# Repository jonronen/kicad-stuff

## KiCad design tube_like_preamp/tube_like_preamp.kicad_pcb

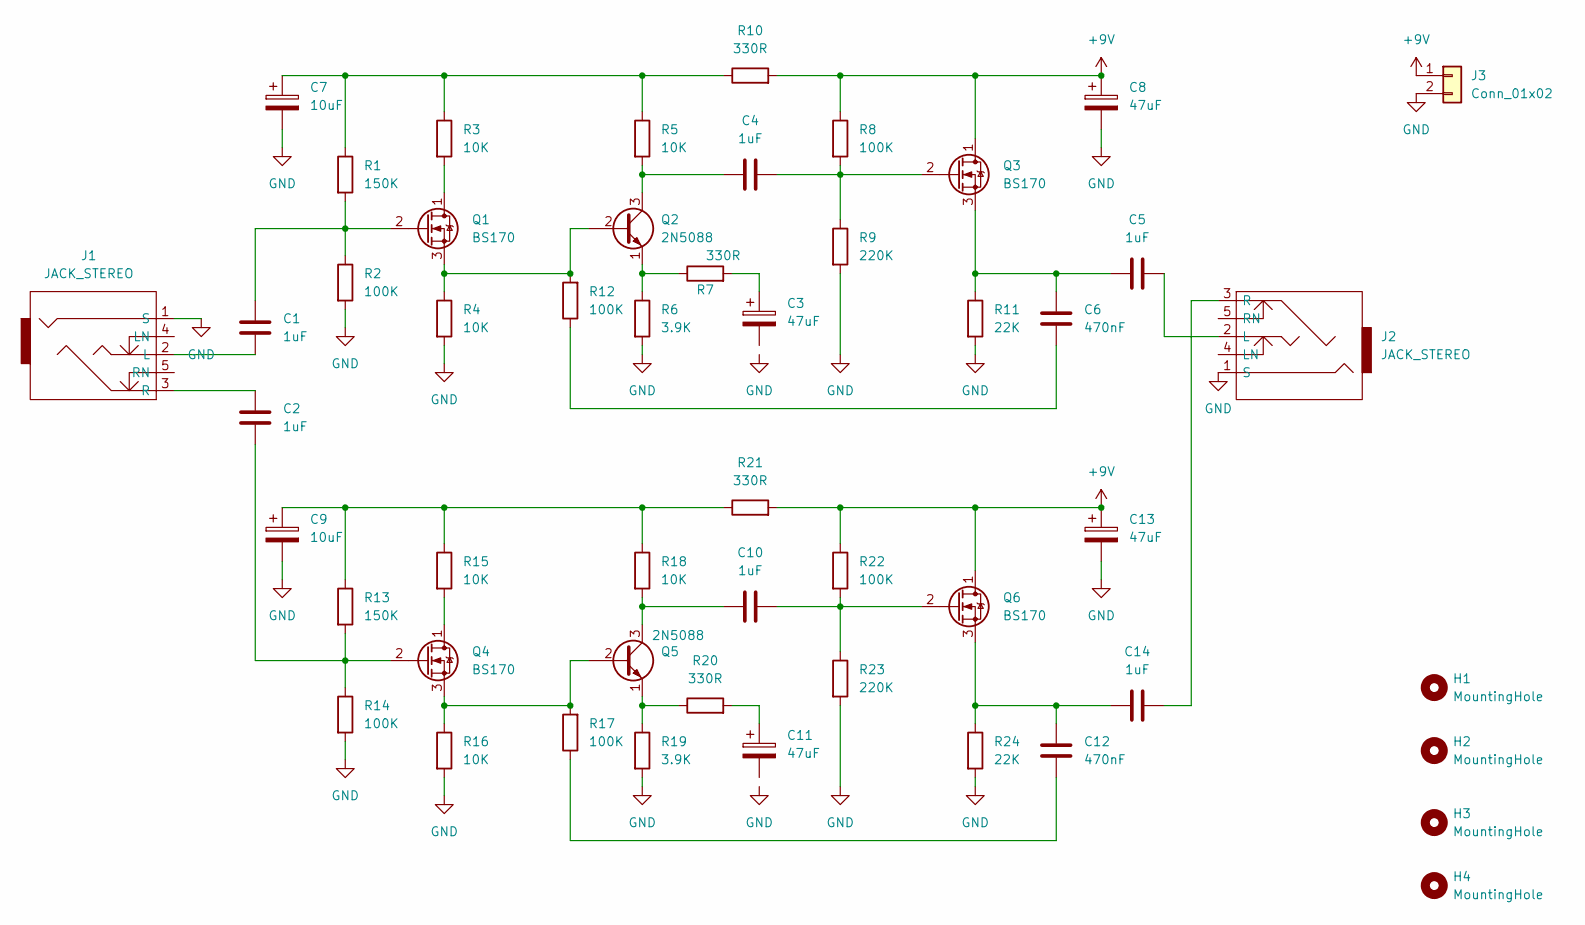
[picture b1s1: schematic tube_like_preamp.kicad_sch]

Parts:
C1, C2, C4, C5, C10, C14: 1uF; C_Disc_D4.7mm_W2.5mm_P5.00mm
C3, C8, C11, C13: 47uF; CP_Radial_D5.0mm_P2.50mm
C6, C12: 470nF; C_Disc_D4.7mm_W2.5mm_P5.00mm
C7, C9: 10uF; CP_Radial_D5.0mm_P2.50mm
H1, H2, H3, H4: MountingHole; MountingHole_3.2mm_M3_DIN965
J1, J2: JACK_STEREO; AUDIO_STEREO_CONN
J3: Conn_01x02; PinHeader_1x02_P2.54mm_Vertical
Q1, Q3, Q4, Q6: BS170; TO-92_Inline
Q2, Q5: 2N5088; TO-92_Inline
R1, R13: 150K; R_Axial_DIN0309_L9.0mm_D3.2mm_P2.54mm_Vertical
R2, R8, R12, R14, R17, R22: 100K; R_Axial_DIN0309_L9.0mm_D3.2mm_P2.54mm_Vertical
R3, R4, R5, R15, R16, R18: 10K; R_Axial_DIN0309_L9.0mm_D3.2mm_P2.54mm_Vertical
R6, R19: 3.9K; R_Axial_DIN0309_L9.0mm_D3.2mm_P2.54mm_Vertical
R7, R10, R20, R21: 330R; R_Axial_DIN0309_L9.0mm_D3.2mm_P2.54mm_Vertical
R9, R23: 220K; R_Axial_DIN0309_L9.0mm_D3.2mm_P2.54mm_Vertical
R11, R24: 22K; R_Axial_DIN0309_L9.0mm_D3.2mm_P2.54mm_Vertical

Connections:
+9V: C8.1, C13.1, J3.1, Q3.1 (D), Q6.1 (D), R8.1, R10.2, R21.2, R22.1
GND: C7.2, C8.2, C9.2, C13.2, J1.1 (S), J2.1 (S), J3.2, R2.2, R4.2, R6.2, R9.2, R11.2, R14.2, R16.2, R19.2, R23.2, R24.2
unnamed: C3.1, R7.2
unnamed: C6.1, R12.1
unnamed: C7.1, R1.1, R3.1, R5.1, R10.1
unnamed: C9.1, R13.1, R15.1, R18.1, R21.1
unnamed: C11.1, R20.2
unnamed: C12.1, R17.1
unnamed: C1.1, J1.2 (L)
unnamed: C2.2, J1.3 (R)
unnamed: C5.1, J2.2 (L)
unnamed: C14.1, J2.3 (R)
unnamed: Q1.1 (D), R3.2
unnamed: C1.2, Q1.2 (G), R1.2, R2.1
unnamed: Q1.3 (S), Q2.2 (B), R4.1, R12.2
unnamed: C4.2, Q2.3 (C), R5.2
unnamed: Q2.1 (E), R6.1, R7.1
unnamed: C4.1, Q3.2 (G), R8.2, R9.1
unnamed: C5.2, C6.2, Q3.3 (S), R11.1
unnamed: Q4.1 (D), R15.2
unnamed: C2.1, Q4.2 (G), R13.2, R14.1
unnamed: Q4.3 (S), Q5.2 (B), R16.1, R17.2
unnamed: C10.2, Q5.3 (C), R18.2
unnamed: Q5.1 (E), R19.1, R20.1
unnamed: C10.1, Q6.2 (G), R22.2, R23.1
unnamed: C12.2, C14.2, Q6.3 (S), R24.1

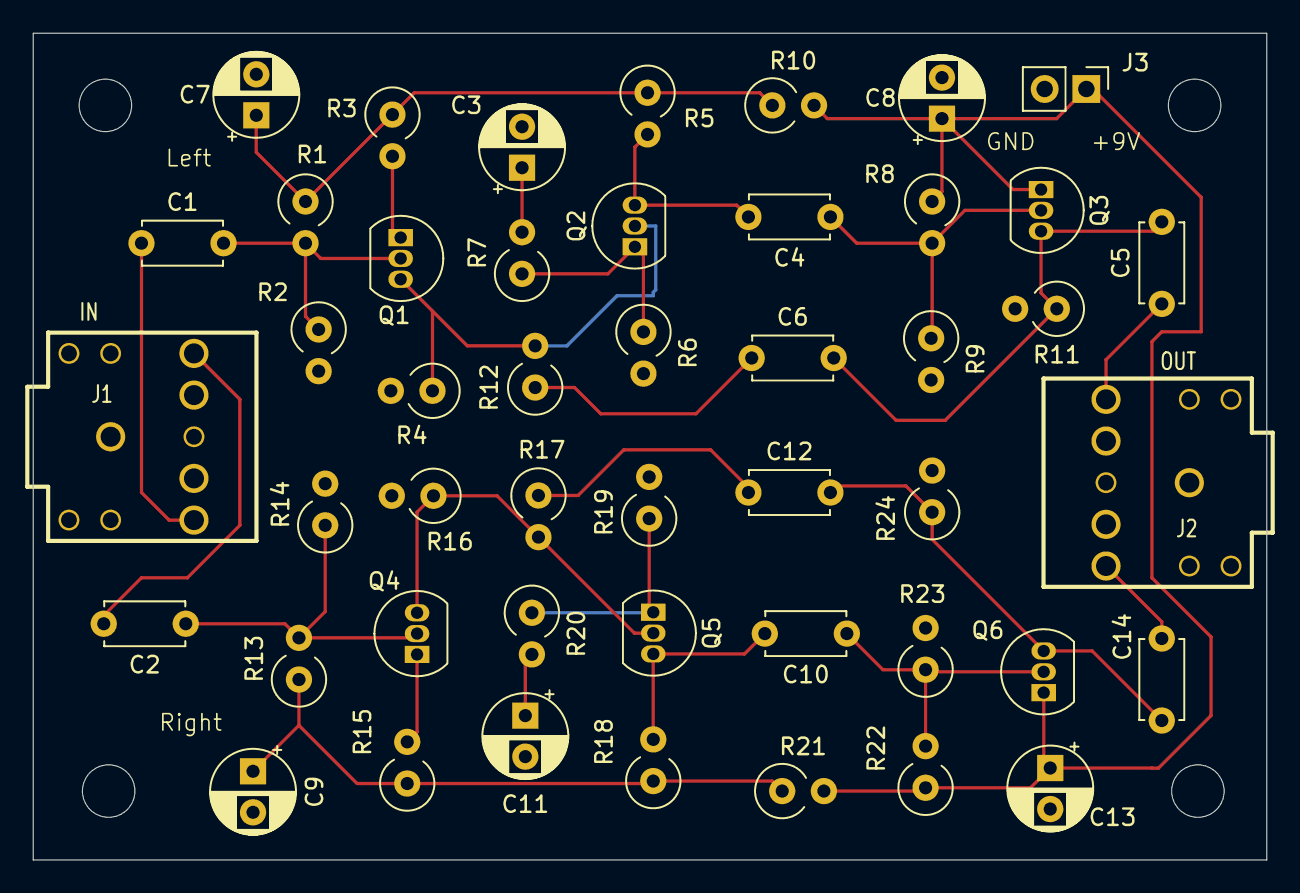
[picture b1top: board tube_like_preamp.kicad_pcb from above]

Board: 2 copper layers, 75.2 x 50.4 mm, 51 parts (0 on the bottom side), 26 nets.

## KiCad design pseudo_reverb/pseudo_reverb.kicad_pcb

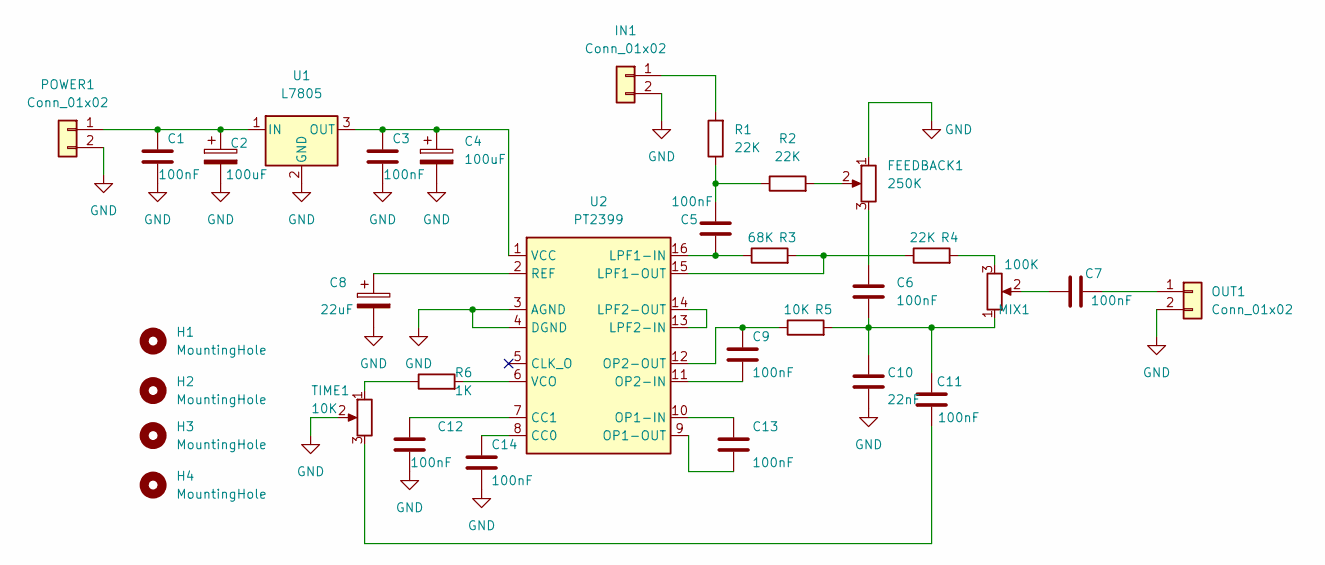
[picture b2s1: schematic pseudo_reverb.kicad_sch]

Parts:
C1, C3, C5, C6, C7, C9, C11, C12, C13, C14: 100nF; C_Disc_D3.0mm_W1.6mm_P2.50mm
C2, C4: 100uF; CP_Radial_D5.0mm_P2.50mm
C8: 22uF; CP_Radial_D5.0mm_P2.50mm
C10: 22nF; C_Disc_D3.0mm_W1.6mm_P2.50mm
FEEDBACK1: 250K; Potentiometer_Alps_RK163_Single_Horizontal
H1, H2, H3, H4: MountingHole; MountingHole_3.2mm_M3_DIN965
IN1: Conn_01x02; Molex_KK-254_AE-6410-02A_1x02_P2.54mm_Vertical
MIX1: 100K; Potentiometer_Alps_RK163_Single_Horizontal
OUT1: Conn_01x02; Molex_KK-254_AE-6410-02A_1x02_P2.54mm_Vertical
POWER1: Conn_01x02; Molex_KK-254_AE-6410-02A_1x02_P2.54mm_Vertical
R1, R2, R4: 22K; C_Disc_D3.0mm_W1.6mm_P2.50mm
R3: 68K; C_Disc_D3.0mm_W1.6mm_P2.50mm
R5: 10K; C_Disc_D3.0mm_W1.6mm_P2.50mm
R6: 1K; C_Disc_D3.0mm_W1.6mm_P2.50mm
TIME1: 10K; Potentiometer_Alps_RK163_Single_Horizontal
U1: L7805; TO-220-3_Vertical
U2: PT2399; DIP-16_W7.62mm

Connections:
GND: C1.2, C2.2, C3.2, C4.2, C8.2, C10.2, C12.2, C14.2, FEEDBACK1.1, IN1.2, OUT1.2, POWER1.2, TIME1.2, U1.2 (GND), U2.3 (AGND), U2.4 (DGND)
unnamed: C1.1, C2.1, POWER1.1, U1.1 (IN)
unnamed: C3.1, C4.1, U1.3 (OUT), U2.1 (VCC)
unnamed: C5.1, R1.1, R2.1
unnamed: C5.2, R3.1, U2.16 (LPF1-IN)
unnamed: C6.1, FEEDBACK1.3
unnamed: C7.1, MIX1.2
unnamed: C7.2, OUT1.1
unnamed: C8.1, U2.2 (REF)
unnamed: C9.1, R5.1, U2.12 (OP2-OUT)
unnamed: C9.2, U2.11 (OP2-IN)
unnamed: C6.2, C10.1, C11.2, MIX1.1, R5.2
unnamed: C11.1, TIME1.3
unnamed: C12.1, U2.7 (CC1)
unnamed: C13.1, U2.10 (OP1-IN)
unnamed: C13.2, U2.9 (OP1-OUT)
unnamed: C14.1, U2.8 (CC0)
unnamed: FEEDBACK1.2, R2.2
unnamed: IN1.1, R1.2
unnamed: MIX1.3, R4.2
unnamed: R3.2, R4.1, U2.15 (LPF1-OUT)
unnamed: R6.1, TIME1.1
unnamed: R6.2, U2.6 (VCO)
unnamed: U2.13 (LPF2-IN), U2.14 (LPF2-OUT)

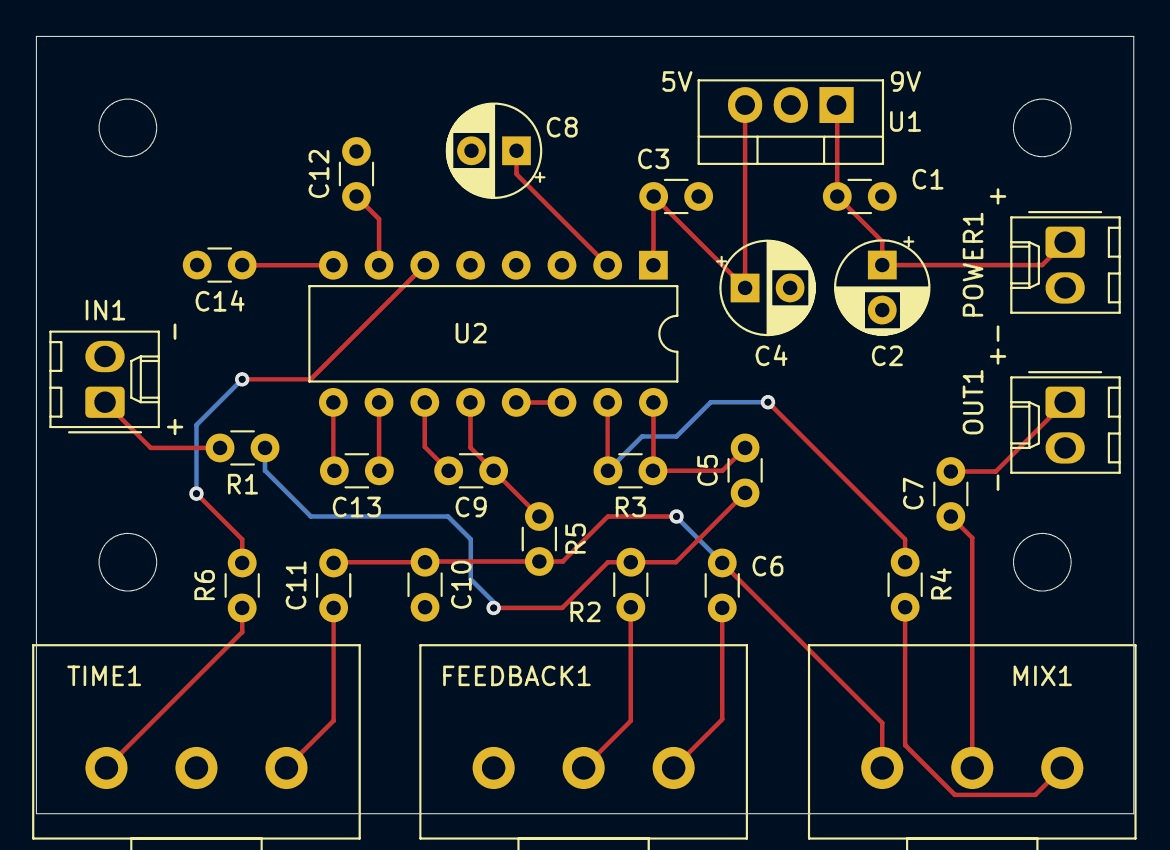
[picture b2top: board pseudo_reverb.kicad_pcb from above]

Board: 2 copper layers, 61.0 x 43.2 mm, 32 parts (0 on the bottom side), 24 nets.

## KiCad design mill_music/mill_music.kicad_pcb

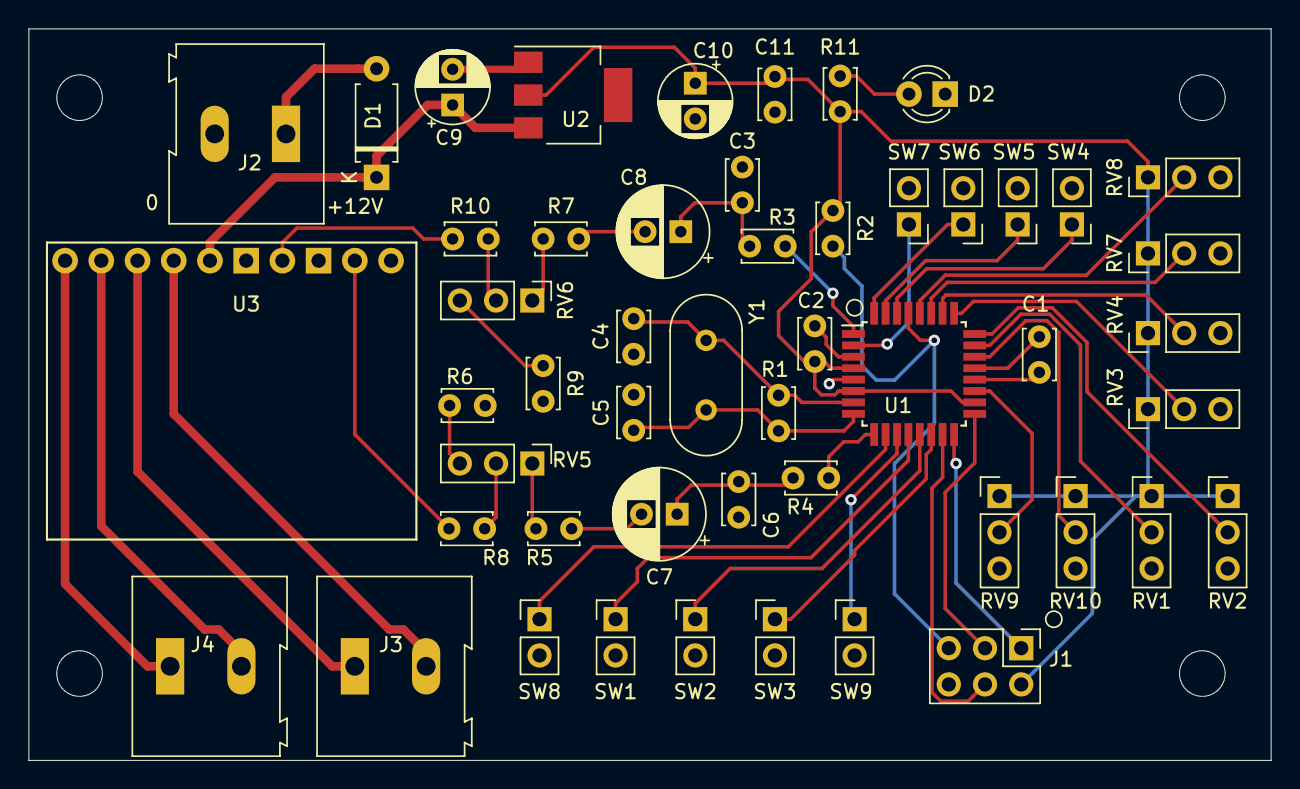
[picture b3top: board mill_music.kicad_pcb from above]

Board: 2 copper layers, 87.1 x 51.3 mm, 55 parts (0 on the bottom side), 47 nets.

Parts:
C1, C2, C11: 100nF; C_Disc_D3.4mm_W2.1mm_P2.50mm
C3, C6: 33nF; C_Disc_D3.4mm_W2.1mm_P2.50mm
C4, C5: 22pF; C_Disc_D3.4mm_W2.1mm_P2.50mm
C7, C8: 100uF; CP_Radial_D6.3mm_P2.50mm
C9, C10: 47uF; CP_Radial_D5.0mm_P2.50mm
D1: D; D_A-405_P7.62mm_Horizontal
D2: LED; LED_D3.0mm
H1, H2, H3, H4: MountingHole; MountingHole_3.2mm_M3_ISO14580
J1: Conn_02x03_Odd_Even; PinHeader_2x03_P2.54mm_Vertical
J2, J3, J4: Screw_Terminal_01x02; TerminalBlock_Altech_AK300-2_P5.00mm
R1: 1M; C_Disc_D3.4mm_W2.1mm_P2.50mm
R2: 10K; C_Disc_D3.4mm_W2.1mm_P2.50mm
R3, R4: 2.2K; C_Disc_D3.4mm_W2.1mm_P2.50mm
R5, R7: 47K; C_Disc_D3.4mm_W2.1mm_P2.50mm
R6, R8, R9, R10, R11: 1K; C_Disc_D3.4mm_W2.1mm_P2.50mm
RV1, RV2, RV3, RV4, RV7, RV8, RV9, RV10: 47K; PinHeader_1x03_P2.54mm_Vertical
RV5, RV6: 10K; PinHeader_1x03_P2.54mm_Vertical
SW1, SW2, SW3, SW4, SW5, SW6, SW7, SW8, SW9: SW_Push; PinHeader_1x02_P2.54mm_Vertical
U1: ATmega328-AU; TQFP-32_7x7mm_P0.8mm
U2: LM1117-5.0; SOT-223-3_TabPin2
U3: OEP30Wx2-Module; OEP30Wx2
Y1: 16MHz; Crystal_HC49-U_Vertical

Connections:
+5V: C2.1, C10.1, C11.2, J1.2, R2.1, R11.2, RV1.1, RV2.1, RV3.1, RV4.1, RV7.1, RV8.1, RV9.1, RV10.1, U1.4, U1.6, U1.18, U2.2
+12V: C9.1, D1.1, U2.3, U3.5
/ADC0: RV1.2, U1.23
/ADC1: RV2.2, U1.24
/ADC2: RV3.2, U1.25
/ADC3: RV4.2, U1.26
/ADC4: RV7.2, U1.27
/ADC5: RV8.2, U1.28
/ADC6: RV9.2, U1.19
/ADC7: RV10.2, U1.22
/BTN1: SW1.1, U1.12
/BTN2: SW2.1, U1.13
/BTN3: SW3.1, U1.14
/BTN4: SW4.1, U1.30
/BTN5: SW5.1, U1.31
/BTN6: SW6.1, U1.32
/BTN7: SW7.1, U1.2
/BTN8: SW8.1, U1.10
/BTN9: SW9.1, U1.11
GND: C1.2, C2.2, C3.2, C4.1, C5.1, C6.2, C9.2, C10.2, C11.1, D2.1, J1.6, J2.2, R6.1, R9.2, RV1.3, RV2.3, RV3.3, RV4.3, RV7.3, RV8.3, RV9.3, RV10.3, SW1.2, SW2.2, SW3.2, SW4.2, SW5.2, SW6.2, SW7.2, SW8.2, SW9.2, U1.3, U1.5, U1.21, U2.1, U3.6, U3.8
unnamed: C1.1, U1.20
unnamed: C3.1, C8.1, R3.1
unnamed: C4.2, R1.1, U1.7, Y1.1
unnamed: C5.2, R1.2, U1.8, Y1.2
unnamed: C6.1, C7.1, R4.1
unnamed: C7.2, R5.2
unnamed: C8.2, R7.2
unnamed: D1.2, J2.1
unnamed: D2.2, R11.1
unnamed: J1.1, U1.16
unnamed: J1.3, U1.17
unnamed: J1.4, U1.15
unnamed: J1.5, R2.2, U1.29
unnamed: J3.1, U3.3
unnamed: J3.2, U3.4
unnamed: J4.1, U3.1
unnamed: J4.2, U3.2
unnamed: R3.2, U1.1
unnamed: R4.2, U1.9
unnamed: R5.1, RV5.1
unnamed: R6.2, RV5.3
unnamed: R7.1, RV6.1
unnamed: R8.1, U3.9
unnamed: R8.2, RV5.2
unnamed: R9.1, RV6.3
unnamed: R10.1, U3.7
unnamed: R10.2, RV6.2

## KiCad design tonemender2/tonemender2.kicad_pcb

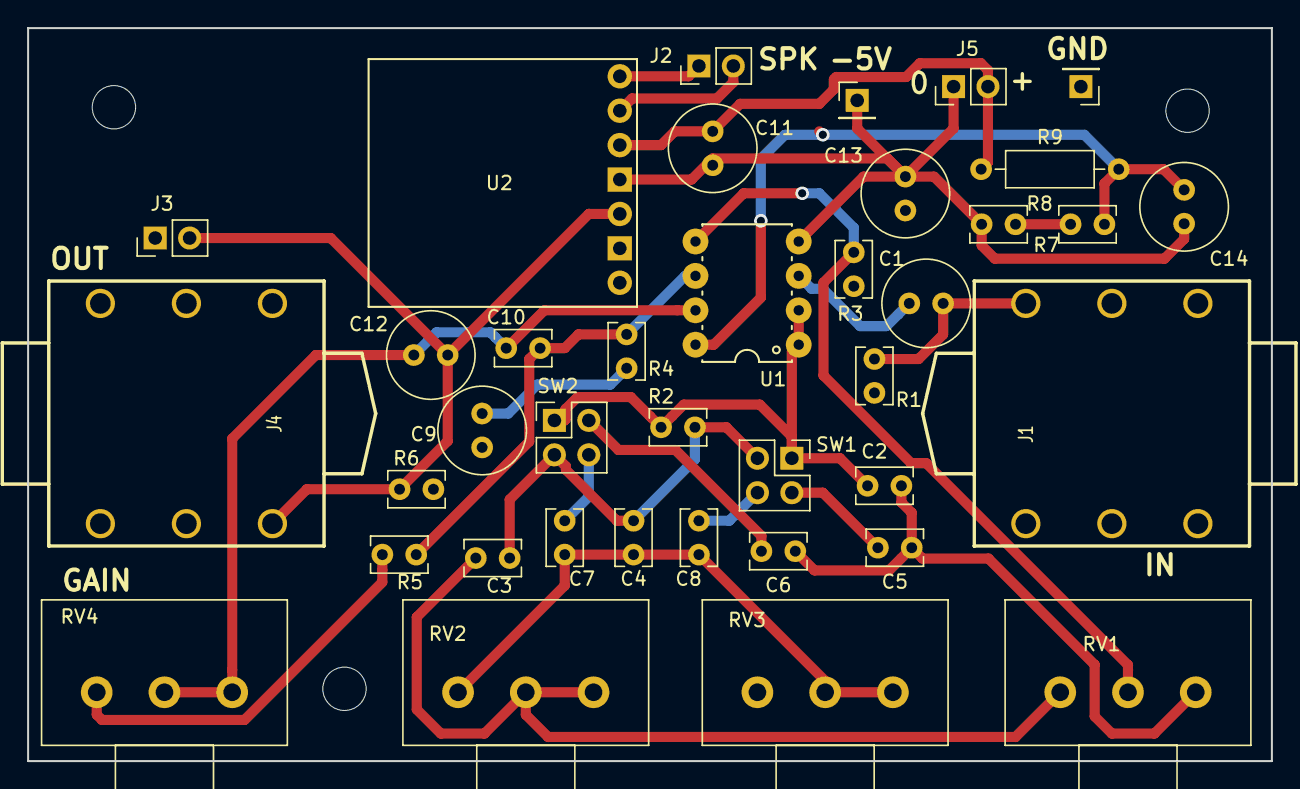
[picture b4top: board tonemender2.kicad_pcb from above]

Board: 2 copper layers, 91.8 x 54.1 mm, 41 parts (0 on the bottom side), 23 nets.

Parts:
C1, C12: 1uF; C_Radial_D6.3mm_H5.0mm_P2.50mm
C2, C6: 80pF; C_Rect_L4.0mm_W2.5mm_P2.50mm
C3: 47nF; C_Rect_L4.0mm_W2.5mm_P2.50mm
C4, C7: 10nF; C_Rect_L4.0mm_W2.5mm_P2.50mm
C5: 150pF; C_Rect_L4.0mm_W2.5mm_P2.50mm
C8: 22nF; C_Rect_L4.0mm_W2.5mm_P2.50mm
C9, C11: 47uF; C_Radial_D6.3mm_H5.0mm_P2.50mm
C10: 47pF (optional); C_Rect_L4.0mm_W2.5mm_P2.50mm
C13, C14: 100uF; C_Radial_D6.3mm_H7.0mm_P2.50mm
H1, H2, H3: MountingHole; MountingHole_3.2mm_M3
J1, J4: JACK_STEREO; audio_635mm_stereo_input
J2, J3, J5: Conn_01x02; PinHeader_1x02_P2.54mm_Vertical
P1, P2: CONN_01X01; PinHeader_1x01_P2.54mm_Vertical
R1, R3, R6: 1M; C_Rect_L4.0mm_W2.5mm_P2.50mm
R2: 200K; C_Rect_L4.0mm_W2.5mm_P2.50mm
R4: 4.7K; C_Rect_L4.0mm_W2.5mm_P2.50mm
R5: 620R; C_Rect_L4.0mm_W2.5mm_P2.50mm
R7, R8: 100K; C_Rect_L4.0mm_W2.5mm_P2.50mm
R9: 10R; R_Axial_DIN0207_L6.3mm_D2.5mm_P10.16mm_Horizontal
RV1, RV2: 500K; Potentiometer_Alps_RK163_Single_Horizontal
RV3: 50K; Potentiometer_Alps_RK163_Single_Horizontal
RV4: 10K; Potentiometer_Alps_RK163_Single_Horizontal
SW1, SW2: SW_DPST_x2; PinHeader_2x02_P2.54mm_Vertical
U1: OPA1612; PDIP-8
U2: OEP30W-Module; OEP30W

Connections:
+5V: C14.1, R7.1, R9.2, U1.8
-5V: C11.2, C13.2, C14.2, J5.1, P2.1, R8.2, U1.4, U2.4
/PWR: C11.1, J5.2, R9.1, U2.3
/PreAmpOut: C12.1, J3.2, J4.2, R6.1, U2.5
GND: C9.2, C13.1, J1.1, J1.4, J1.5, J3.1, J4.1, J4.4, J4.5, P1.1, R1.2, R3.2, R6.2, R7.2, R8.1, RV3.1, U2.6
unnamed: C1.1, U1.3
unnamed: C1.2, J1.2, R1.1
unnamed: C2.1, C5.1, C6.1, RV1.3
unnamed: C2.2, R2.1, SW1.1, SW2.1, U1.1, U1.2
unnamed: C3.1, RV1.1, RV2.2, RV2.3
unnamed: C3.2, C4.2, R2.2, SW1.3, SW2.3
unnamed: C4.1, C7.1, C8.1, RV2.1, RV3.2, RV3.3
unnamed: C5.2, SW1.2
unnamed: C6.2, SW2.2
unnamed: C7.2, SW2.4
unnamed: C8.2, SW1.4
unnamed: C9.1, R4.2
unnamed: C10.1, C12.2, RV4.2, RV4.3, U1.7
unnamed: C10.2, R4.1, R5.2, U1.6
unnamed: J2.1, U2.1
unnamed: J2.2, U2.2
unnamed: R3.1, RV1.2, U1.5
unnamed: R5.1, RV4.1

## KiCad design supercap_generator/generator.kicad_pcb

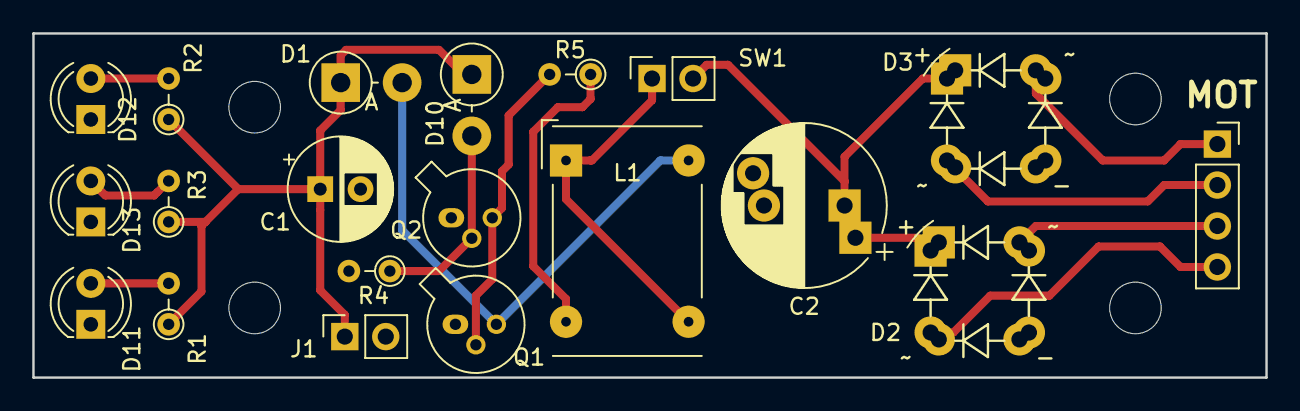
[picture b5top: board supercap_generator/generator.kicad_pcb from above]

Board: 2 copper layers, 76.5 x 21.3 mm, 20 parts (0 on the bottom side), 15 nets.

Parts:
C1: 100uF; CP_Radial_D6.3mm_P2.50mm
C2: 1F; CP_Radial_D10.0mm_P5.00mm_P7.50mm
D1: 1N5817; D_DO-15_P3.81mm_Vertical_AnodeUp
D2, D3: D_Bridge_+A-A; DiodeBridge
D10: ZPYxx; D_DO-15_P3.81mm_Vertical_AnodeUp
D11, D12, D13: LED; LED_D4.0mm
J1: Conn_01x02_Male; PinSocket_1x02_P2.54mm_Vertical
J2: Conn_01x04_Male; PinSocket_1x04_P2.54mm_Vertical
L1: L_Core_Ferrite_Coupled; Choke_Schaffner_RN204-04-9.0x14.0mm
Q1, Q2: PN2222A; TO-18-3
R1, R2, R3, R4, R5: R; R_Axial_DIN0204_L3.6mm_D1.6mm_P2.54mm_Vertical
SW1: SW_SPST; PinSocket_1x02_P2.54mm_Vertical

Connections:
unnamed: C1.1, D1.1, D10.1, J1.1, R1.1, R2.1, R3.1
unnamed: C1.2, C2.2, D2.3, D3.3, D11.1, D12.1, D13.1, J1.2, Q1.1, Q2.1, R4.2
unnamed: C2.1, D2.1, D3.1, SW1.2
unnamed: D1.2, L1.2, Q1.3
unnamed: D2.2, J2.4
unnamed: D2.4, J2.3
unnamed: D3.2, J2.2
unnamed: D3.4, J2.1
unnamed: D10.2, Q2.2, R4.1
unnamed: D11.2, R1.2
unnamed: D12.2, R2.2
unnamed: D13.2, R3.2
unnamed: L1.1, L1.4, SW1.1
unnamed: L1.3, R5.1
unnamed: Q1.2, Q2.3, R5.2

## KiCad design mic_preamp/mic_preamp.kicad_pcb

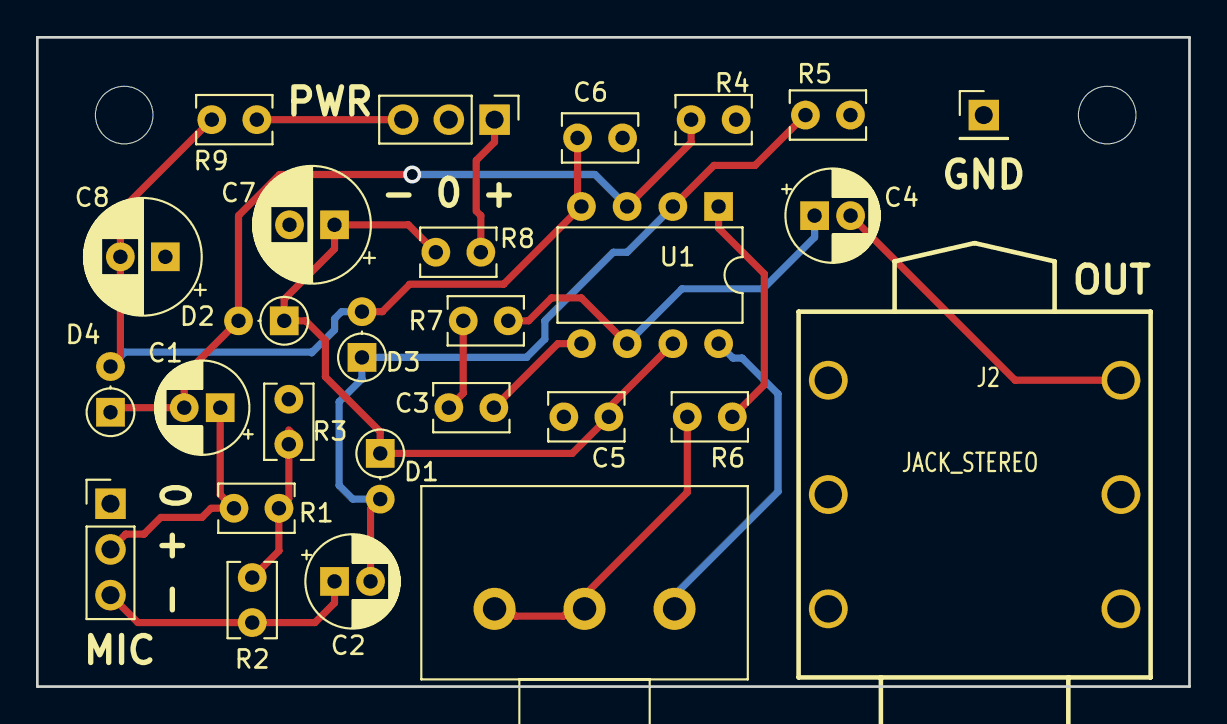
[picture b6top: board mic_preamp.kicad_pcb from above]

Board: 2 copper layers, 64.0 x 36.1 mm, 29 parts (0 on the bottom side), 17 nets.

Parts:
C1, C2: 47uF; CP_Radial_D5.0mm_P2.00mm
C3, C5, C6: 100n; C_Rect_L4.0mm_W2.5mm_P2.50mm
C4: 1uF; CP_Radial_D5.0mm_P2.00mm
C7, C8: 100uF; CP_Radial_D6.3mm_P2.50mm
D1, D2, D3, D4: 1N4148; D_DO-35_SOD27_P2.54mm_Vertical_AnodeUp
H1, H2: MountingHole; MountingHole_3.2mm_M3
J1, J3: Conn_01x03; PinHeader_1x03_P2.54mm_Vertical
J2: JACK_STEREO; audio_635mm_stereo_input
J4: Conn_01x01; PinHeader_1x01_P2.54mm_Vertical
R1, R2: 6.8K; C_Rect_L4.0mm_W2.5mm_P2.50mm
R3: 47K; C_Rect_L4.0mm_W2.5mm_P2.50mm
R4, R5: 2.2K; C_Rect_L4.0mm_W2.5mm_P2.50mm
R6: 100R; C_Rect_L4.0mm_W2.5mm_P2.50mm
R7: 1M; C_Rect_L4.0mm_W2.5mm_P2.50mm
R8, R9: 10R; C_Rect_L4.0mm_W2.5mm_P2.50mm
RV1: 2.2K; Potentiometer_Alps_RK163_Single_Horizontal
U1: INA217; DIP-8_W7.62mm

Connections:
+15V: C5.1, C7.1, D1.1, D2.1, R8.2, U1.7
-15V: C6.2, C8.2, D3.2, D4.2, R9.2, U1.4
Earth: C5.2, C6.1, C7.2, C8.1, J1.1, J2.1, J3.2, J4.1, R3.2, R4.2, R5.2
unnamed: C1.1, J1.2, R1.1
unnamed: C1.2, D2.2, D4.1, R4.1, U1.3
unnamed: C2.1, J1.3, R2.1
unnamed: C2.2, D1.2, D3.1, R5.1, U1.2
unnamed: C3.1, R7.2
unnamed: C3.2, U1.5
unnamed: C4.1, R7.1, U1.6
unnamed: C4.2, J2.2
unnamed: J3.1, R8.1
unnamed: J3.3, R9.1
unnamed: R1.2, R2.2, R3.1
unnamed: R6.1, U1.1
unnamed: R6.2, RV1.1, RV1.2
unnamed: RV1.3, U1.8

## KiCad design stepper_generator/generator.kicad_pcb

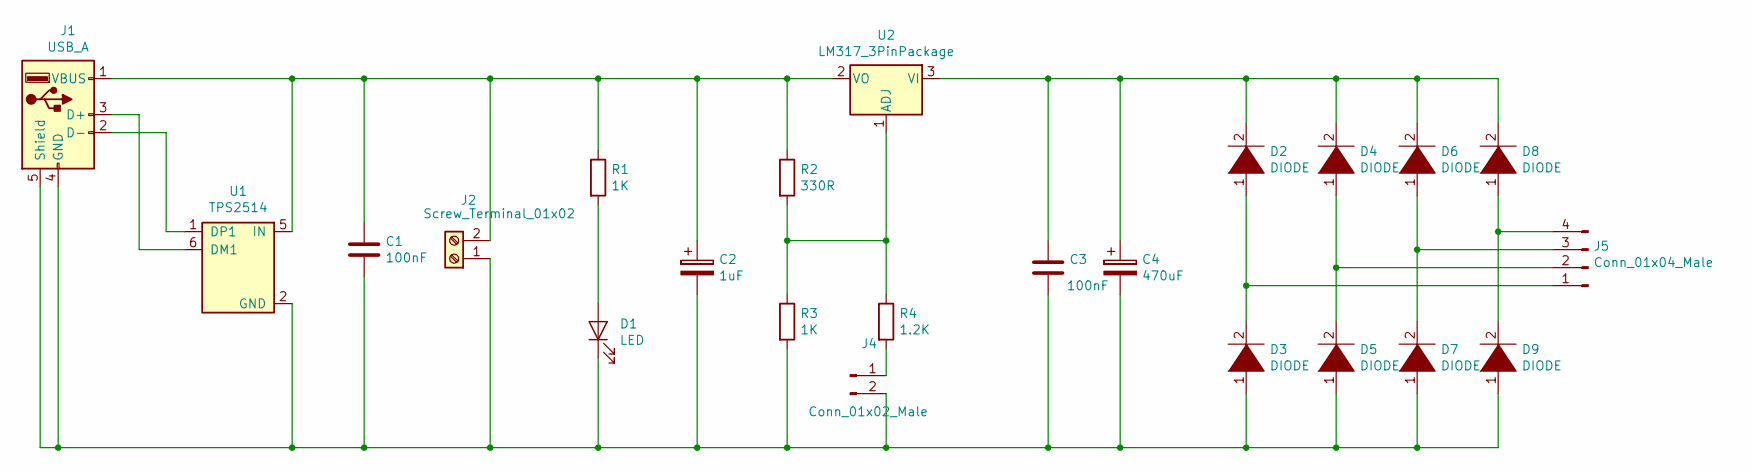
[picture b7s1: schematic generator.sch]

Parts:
C1, C3: 100nF; C_Disc_D3.0mm_W1.6mm_P2.50mm
C2: 1uF; CP_Radial_D5.0mm_P2.50mm
C4: 470uF; CP_Radial_D6.3mm_P2.50mm
D1: LED; LED_D4.0mm
D2, D4, D6, D8: DIODE; D_DO-15_P3.81mm_Vertical_AnodeUp
D3, D5, D7, D9: DIODE; D_DO-15_P3.81mm_Vertical_KathodeUp
J1: USB_A; USB_A_Female
J2: Screw_Terminal_01x02; PinSocket_1x02_P2.54mm_Vertical
J4: Conn_01x02_Male; PinSocket_1x02_P2.54mm_Vertical
J5: Conn_01x04_Male; PinSocket_1x04_P2.54mm_Vertical
R1, R3: 1K; C_Disc_D3.0mm_W1.6mm_P2.50mm
R2: 330R; C_Disc_D3.0mm_W1.6mm_P2.50mm
R4: 1.2K; C_Disc_D3.0mm_W1.6mm_P2.50mm
U1: TPS2514; SOT-23-6
U2: LM317_3PinPackage; TO-220-3_Vertical

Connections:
unnamed: C1.1, C2.1, J1.1 (VBUS), J2.2, R1.1, R2.1, U1.5 (IN), U2.2 (VO)
unnamed: C1.2, C2.2, C3.2, C4.2, D1.1 (K), D3.1 (K), D5.1 (K), D7.1 (K), D9.1 (K), J1.4 (GND), J1.5 (Shield), J2.1, J4.2, R3.2, U1.2 (GND)
unnamed: C3.1, C4.1, D2.2 (A), D4.2 (A), D6.2 (A), D8.2 (A), U2.3 (VI)
unnamed: D1.2 (A), R1.2
unnamed: D2.1 (K), D3.2 (A), J5.1
unnamed: D4.1 (K), D5.2 (A), J5.2
unnamed: D6.1 (K), D7.2 (A), J5.3
unnamed: D8.1 (K), D9.2 (A), J5.4
unnamed: J1.2 (D-), U1.1 (DP1)
unnamed: J1.3 (D+), U1.6 (DM1)
unnamed: J4.1, R4.2
unnamed: R2.2, R3.1, R4.1, U2.1 (ADJ)

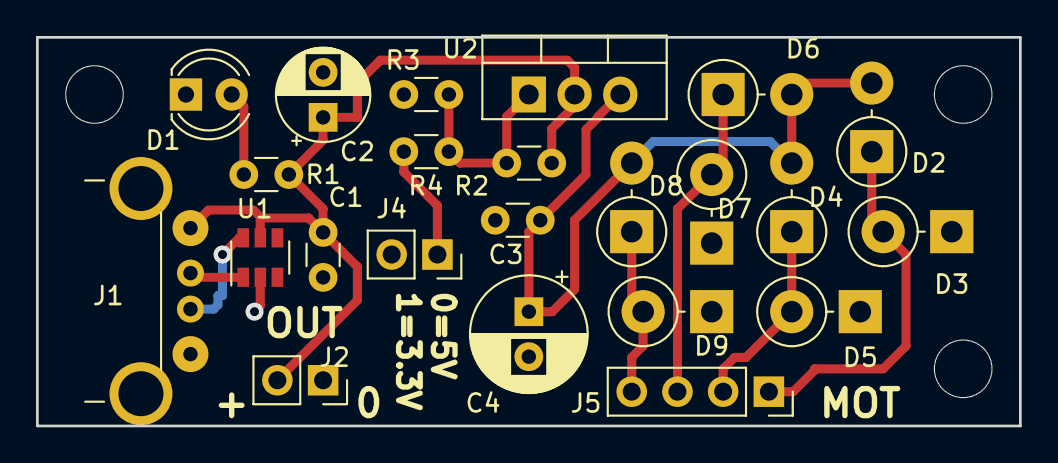
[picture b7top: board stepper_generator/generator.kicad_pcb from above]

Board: 2 copper layers, 54.6 x 21.6 mm, 23 parts (0 on the bottom side), 12 nets.

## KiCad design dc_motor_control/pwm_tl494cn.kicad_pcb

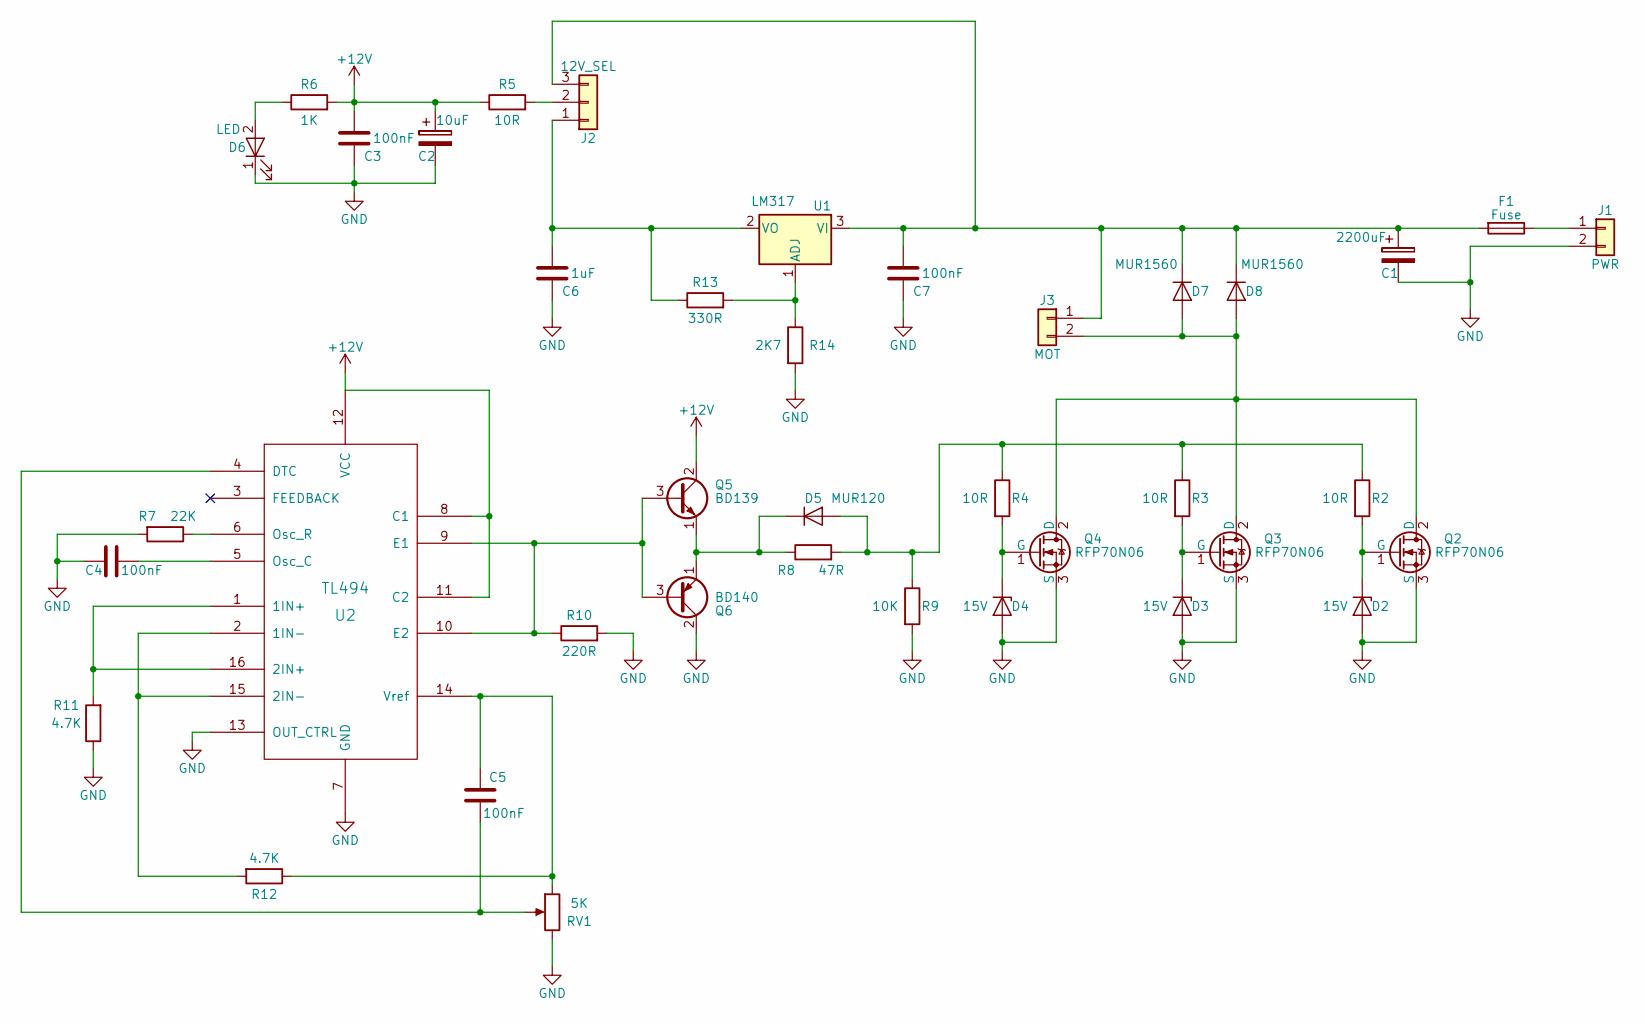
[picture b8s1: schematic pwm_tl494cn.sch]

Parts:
C1: 2200uF; CP_Radial_D12.5mm_P5.00mm
C2: 10uF; CP_Radial_D4.0mm_P2.00mm
C3, C4, C5, C7: 100nF; C_Rect_L4.6mm_W2.0mm_P2.50mm_MKS02_FKP02
C6: 1uF; C_Rect_L4.6mm_W2.0mm_P2.50mm_MKS02_FKP02
D2, D3, D4: 15V; D_T-1_P5.08mm_Horizontal
D5: MUR120; D_T-1_P5.08mm_Horizontal
D6: LED; LED_D4.0mm
D7, D8: MUR1560; TO-220-2_Vertical
F1: Fuse; Fuse_SMD1206_Wave
J1: PWR; TerminalBlock_bornier-2_P5.08mm
J2: 12V_SEL; Pin_Header_Straight_1x03_Pitch2.54mm
J3: MOT; TerminalBlock_bornier-2_P5.08mm
Q2, Q3, Q4: RFP70N06; TO-220-3_Vertical
Q5: BD139; TO-126_Vertical
Q6: BD140; TO-126_Vertical
R2, R3, R4, R5: 10R; C_Rect_L4.6mm_W2.0mm_P2.50mm_MKS02_FKP02
R6: 1K; C_Rect_L4.6mm_W2.0mm_P2.50mm_MKS02_FKP02
R7: 22K; C_Rect_L4.6mm_W2.0mm_P2.50mm_MKS02_FKP02
R8: 47R; C_Rect_L4.6mm_W2.0mm_P2.50mm_MKS02_FKP02
R9: 10K; C_Rect_L4.6mm_W2.0mm_P2.50mm_MKS02_FKP02
R10: 220R; C_Rect_L4.6mm_W2.0mm_P2.50mm_MKS02_FKP02
R11, R12: 4.7K; C_Rect_L4.6mm_W2.0mm_P2.50mm_MKS02_FKP02
R13: 330R; C_Rect_L4.6mm_W2.0mm_P2.50mm_MKS02_FKP02
R14: 2K7; C_Rect_L4.6mm_W2.0mm_P2.50mm_MKS02_FKP02
RV1: 5K; Potentiometer_Piher_T16H_Single_Vertical
U1: LM317; SOT-223-3_TabPin2
U2: TL494; SO-16-N

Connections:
+12V: C2.1, C3.1, Q5.2 (C), R5.1, R6.2, U2.8 (C1), U2.11 (C2), U2.12 (VCC)
GND: C1.2, C2.2, C3.2, C4.2, C6.2, C7.2, D2.2 (A), D3.2 (A), D4.2 (A), D6.1 (K), J1.2, Q2.3 (S), Q3.3 (S), Q4.3 (S), Q6.2 (C), R7.2, R9.2, R10.2, R11.1, R14.2, RV1.3, U2.7 (GND), U2.13 (OUT_CTRL)
unnamed: C1.1, C7.1, D7.1 (K), D8.1 (K), F1.2, J2.3, J3.1, U1.3 (VI)
unnamed: C4.1, U2.5 (Osc_C)
unnamed: C5.1, RV1.2, U2.4 (DTC)
unnamed: C5.2, R12.1, RV1.1, U2.14 (Vref)
unnamed: C6.1, J2.1, R13.1, U1.2 (VO)
unnamed: D2.1 (K), Q2.1 (G), R2.2
unnamed: D3.1 (K), Q3.1 (G), R3.2
unnamed: D4.1 (K), Q4.1 (G), R4.2
unnamed: D5.1 (K), Q5.1 (E), Q6.1 (E), R8.1
unnamed: D5.2 (A), R2.1, R3.1, R4.1, R8.2, R9.1
unnamed: D6.2 (A), R6.1
unnamed: D7.2 (A), D8.2 (A), J3.2, Q2.2 (D), Q3.2 (D), Q4.2 (D)
unnamed: F1.1, J1.1
unnamed: J2.2, R5.2
unnamed: Q5.3 (B), Q6.3 (B), R10.1, U2.9 (E1), U2.10 (E2)
unnamed: R7.1, U2.6 (Osc_R)
unnamed: R11.2, U2.1 (1IN+), U2.16 (2IN+)
unnamed: R12.2, U2.2 (1IN-), U2.15 (2IN-)
unnamed: R13.2, R14.1, U1.1 (ADJ)

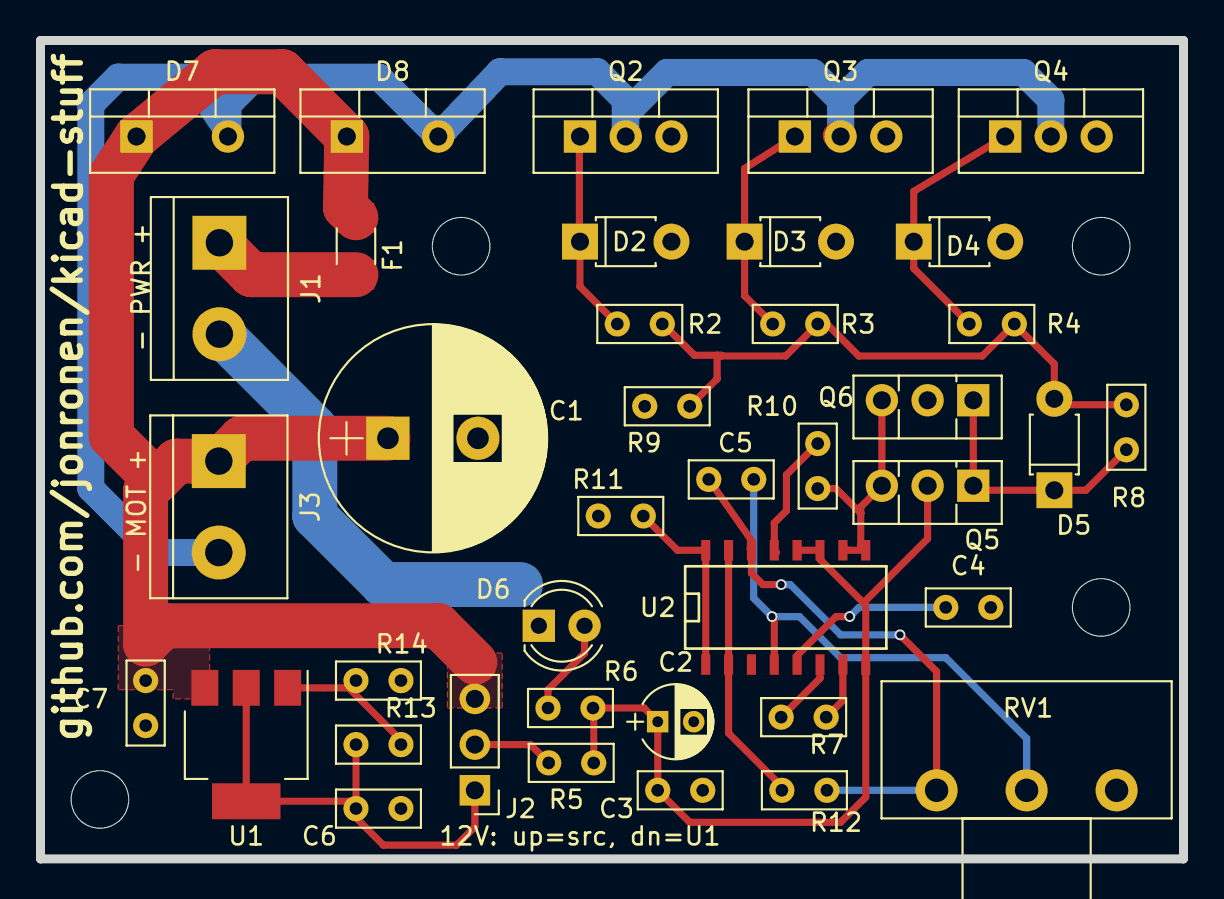
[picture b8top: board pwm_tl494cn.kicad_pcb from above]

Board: 2 copper layers, 63.5 x 45.5 mm, 39 parts (0 on the bottom side), 21 nets.

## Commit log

2016-03-31 adding tonemender and raspi audio shield
2016-05-11 Tonemender for Bass: 1. Updated the capacitor values 2. Shrank the PCB
2016-08-08 bom for PCM3060 rpi shield
2016-09-12 adding a transformer symbol
2016-09-12 new power supply board
2016-09-18 power supply update
2016-09-21 New transformer footprint, updated power PCB
2016-09-21 Adding a CUT OUT text for Osh Park
2017-07-19 adding a limit switch footprint
2017-09-07 use bigger holes for A4988
2017-09-07 use smaller holes for the big limit switch
2018-01-05 adding rgb led board and some shit
2018-01-07 RGB LED minor PCB changes
2018-01-13 adding resistor values
2018-09-11 New TL494 symbol and a new DC motor controller based on TL494
2018-09-14 New PCB for DC motor control
2018-09-14 Refining the DC motor control some more
2018-09-21 some more minor changes to the DC motor control PCB
2018-09-26 add a TQFP-32 footprint
2018-11-27 New PCB: generator based on stepper motor
2018-11-27 New footprint for USB type A female connector
2018-11-27 Modify the USB A female footprint to comply with OSHpark settings
2018-12-21 Change the pin layout of the USB connector
2018-12-21 Flip the USB connector on the stepper generator
2018-12-21 Add a source text to the stepper generator board
2019-10-11 Add an INA217-based mic preamp
2019-11-22 Minor changes to the INA-217 based mic preamp
2020-09-20 Add a PDF with the schematic
2021-11-25 New symbols and footprints
2021-11-25 New generator
2021-11-25 New project: music workshop
2021-11-28 Add LED, diode, and extra capacitor
2021-12-11 Mill Music: Add the PCB
2021-12-11 Mill Music: add copyright and PDF
2021-12-11 Mill Music: add more text on the board
2021-12-13 Mill Music: update footprints and PCB
2022-01-25 New symbols and footprints for OEP30W
2022-01-25 New tonemender
2022-01-26 Improve tonemender2 PCB
2022-01-26 Update copyright on tonemender2
2022-01-26 Fix edge cuts on tonemender2
2022-01-30 New music platform revision
2022-04-22 schematics for RPI audio shield
2023-04-28 New pseudo-reverb
    Based on:
    http://tagboardeffects.blogspot.com/2012/03/ersatz-verben-psuedo-reverb-by.html
2023-04-28 Add power notations in pseudo reverb board
2024-09-26 Tube-like preamp
2024-12-01 Improve Tube-Like Preamp

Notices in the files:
tonemender2/tonemender2.kicad_pcb:
(C) 2014-2022
